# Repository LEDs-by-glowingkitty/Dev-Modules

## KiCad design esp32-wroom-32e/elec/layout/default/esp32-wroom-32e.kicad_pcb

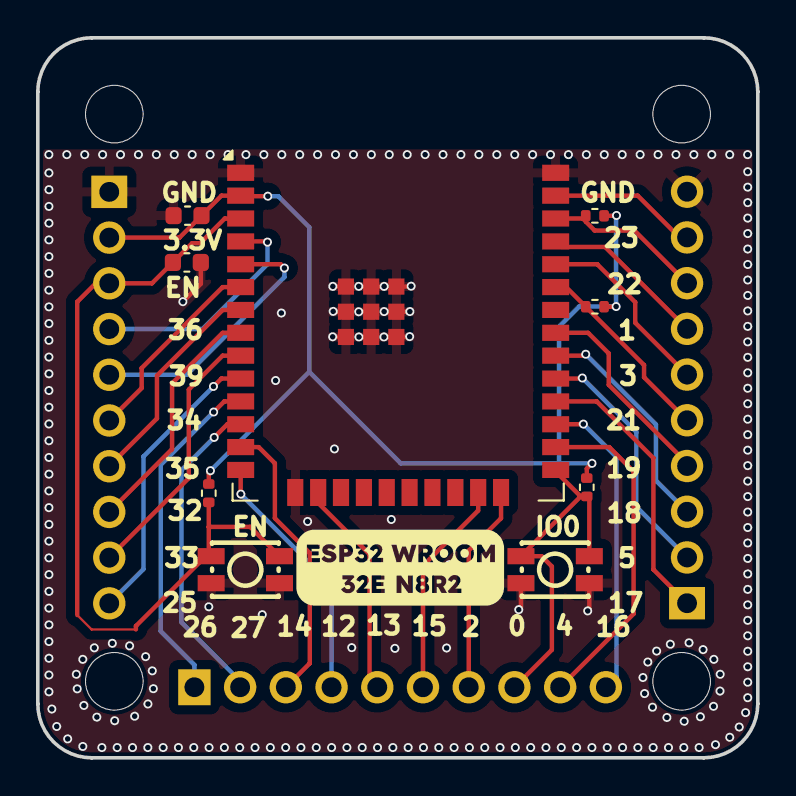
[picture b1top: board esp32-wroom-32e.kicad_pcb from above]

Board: 2 copper layers, 40.0 x 40.0 mm, 16 parts (0 on the bottom side), 29 nets.

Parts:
C1: 10V 10uF X5R ±10% 0603 Multilayer Ceramic Capacit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; C0603
C2: 50V 1uF X5R ±10% 0603 Multilayer Ceramic Capacito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; C0603
R1, R2: 62.5mW Thick Film Resistors 50V ±100ppm/℃ ±1% 2kΩ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; R0402
R3: 62.5mW Thick Film Resistors 50V ±100ppm/℃ ±1% 5.1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; R0402
R4: 62.5mW Thick Film Resistors 50V ±100ppm/℃ ±1% 100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; R0402
U1: WIFI-SMD_ESP32-WROOM-32E
U2, U3: SW-SMD_4P-L3.7-W3.0-P1.50-LS4.7
U4, U5, U6: CONN-TH_10P-P2.54_MX128-2.54-10P-GN01-CU-Y-A
U7, U8, U9, U10: MountingHole_3.2mm_M3

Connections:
gnd: C1.2, C2.2, U1.1, U1.15, U1.38, U1.39, U2.2, U3.2, U4.1, U6.10
ic-sck: U1.10, U4.10
ic-sck-1: U1.26, U5.9
io0: R4.1, U1.25, U3.1, U5.8
io2: U1.24, U5.7
io5: U1.29, U6.2
io16: U1.27, U5.10
io17: U1.28, U6.1
io18: U1.30, U6.3
io19: U1.31, U6.4
io27: U1.12, U5.2
io32: U1.8, U4.8
io33: U1.9, U4.9
io34: U1.6, U4.6
io35: U1.7, U4.7
reset: C2.1, R3.1, U1.3, U2.1, U4.3
rx: U1.34, U6.6
scl: R2.1, U1.36, U6.8
sd: U1.11, U5.1
sda: R1.1, U1.33, U6.5
sensor_vn: U1.5, U4.5
sensor_vp: U1.4, U4.4
tck: U1.16, U5.5
tdi: U1.14, U5.4
tdo: U1.23, U5.6
tms: U1.13, U5.3
tx: U1.35, U6.7
vcc: C1.1, R1.2, R2.2, R3.2, R4.2, U1.2, U4.2
ws: U1.37, U6.9

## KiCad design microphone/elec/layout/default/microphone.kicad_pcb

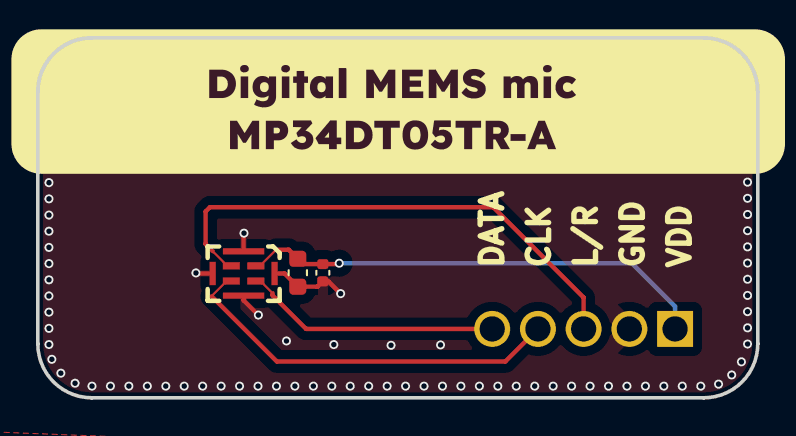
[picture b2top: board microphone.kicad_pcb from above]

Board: 2 copper layers, 40.0 x 20.0 mm, 6 parts (0 on the bottom side), 5 nets.

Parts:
C1: 25V 10uF X5R ±20% 0603 Multilayer Ceramic Capacit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; C0603
C2: 16V 100nF X7R ±10% 0402 Multilayer Ceramic Capaci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; C0402
U1: MIC-SMD_5P-L3.0-W4.0-P0.85-BL
U2: CONN-TH_XY308-2.54-5P
U3, U4: MountingHole_3.2mm_M3

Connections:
clk: U1.3, U2.4
data: U1.4, U2.5
gnd: C1.2, C2.2, U1.5, U2.2
l_r: U1.2, U2.3
vdd: C1.1, C2.1, U1.1, U2.1
